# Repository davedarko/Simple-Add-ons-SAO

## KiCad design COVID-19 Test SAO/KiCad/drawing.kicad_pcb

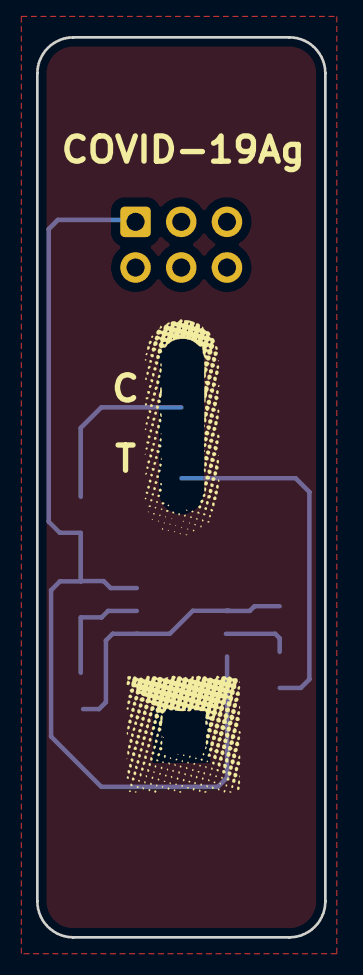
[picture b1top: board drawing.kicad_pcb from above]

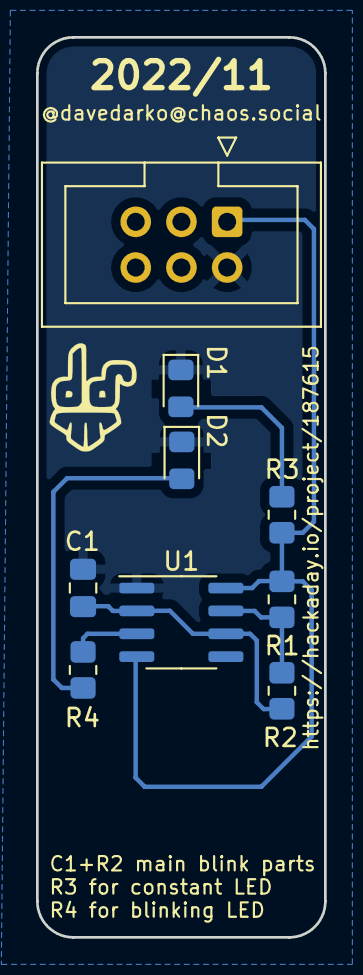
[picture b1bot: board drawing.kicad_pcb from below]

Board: 2 copper layers, 16.0 x 50.0 mm, 11 parts (10 on the bottom side), 7 nets.

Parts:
C1: 1uF; C_0805_2012Metric_Pad1.18x1.45mm_HandSolder
D1, D2: LED; LED_0805_2012Metric_Pad1.15x1.40mm_HandSolder
J1: Conn_02x03_Odd_Even; IDC-Header_2x03_P2.54mm_Vertical
R1, R3, R4: 1k; R_0805_2012Metric_Pad1.20x1.40mm_HandSolder
R2: 470k; R_0805_2012Metric_Pad1.20x1.40mm_HandSolder
Ref**: Val**; finalShadow
Ref**#2: Val**; davedarko_logo_silk_ext
U1: NE555D; SOIC-8_3.9x4.9mm_P1.27mm

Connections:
GND: C1.2, D1.1 (K), D2.1 (K), J1.2, U1.1 (GND)
unnamed: C1.1, R2.2, U1.2 (TR), U1.6 (THR)
unnamed: D1.2 (A), R3.2
unnamed: D2.2 (A), R4.2
unnamed: R1.2, R2.1, U1.7 (DIS)
unnamed: R4.1, U1.3 (Q)
VCC: J1.1, R1.1, R3.1, U1.4 (R), U1.8 (VCC)

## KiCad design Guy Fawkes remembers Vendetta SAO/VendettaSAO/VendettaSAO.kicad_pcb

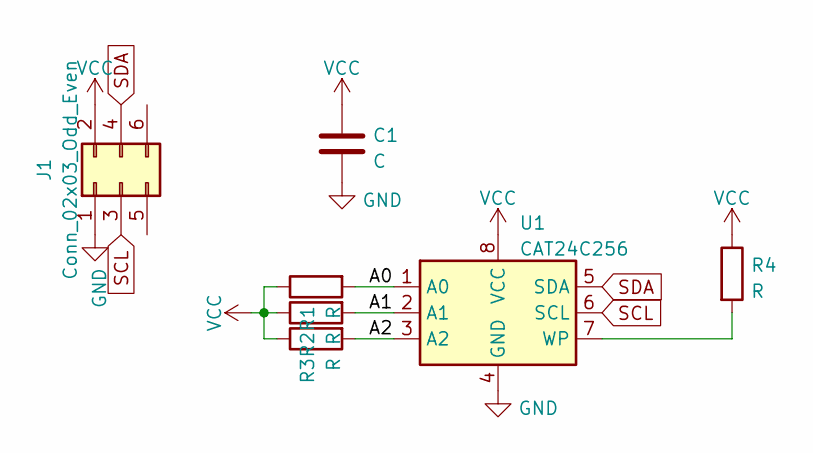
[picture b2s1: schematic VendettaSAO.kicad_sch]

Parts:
C1: C; C_0805_2012Metric_Pad1.18x1.45mm_HandSolder
J1: Conn_02x03_Odd_Even; PinSocket_2x03_P2.54mm_Vertical_SMD
R1, R2, R3, R4: R; R_0805_2012Metric_Pad1.20x1.40mm_HandSolder
U1: CAT24C256; SOIC-8_5.23x5.23mm_P1.27mm

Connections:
/A0: R1.2, U1.1 (A0)
/A1: R2.2, U1.2 (A1)
/A2: R3.2, U1.3 (A2)
GND: C1.2, J1.1, U1.4 (GND)
unnamed: R4.2, U1.7 (WP)
SCL: J1.3, U1.6 (SCL)
SDA: J1.4, U1.5 (SDA)
VCC: C1.1, J1.2, R1.1, R2.1, R3.1, R4.1, U1.8 (VCC)

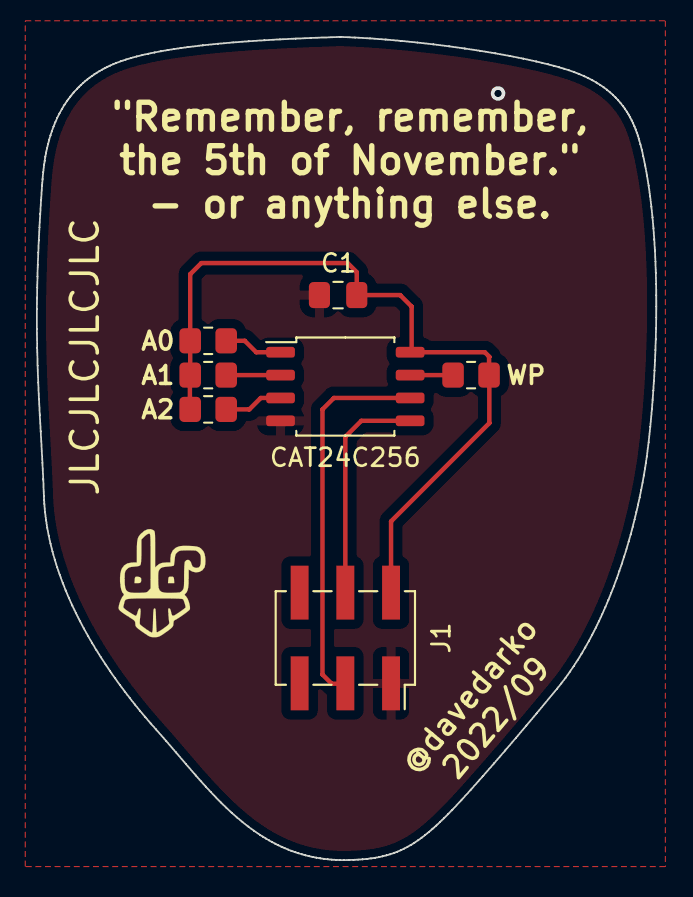
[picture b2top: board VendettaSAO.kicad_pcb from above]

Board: 2 copper layers, 34.4 x 45.7 mm, 10 parts (2 on the bottom side), 8 nets.

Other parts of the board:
Ref**: Val**; davedarko_logo_silk_outline
Ref**#2: Val**; vendettaSAO
Ref**#3: Val**; vendettaSAO_outline

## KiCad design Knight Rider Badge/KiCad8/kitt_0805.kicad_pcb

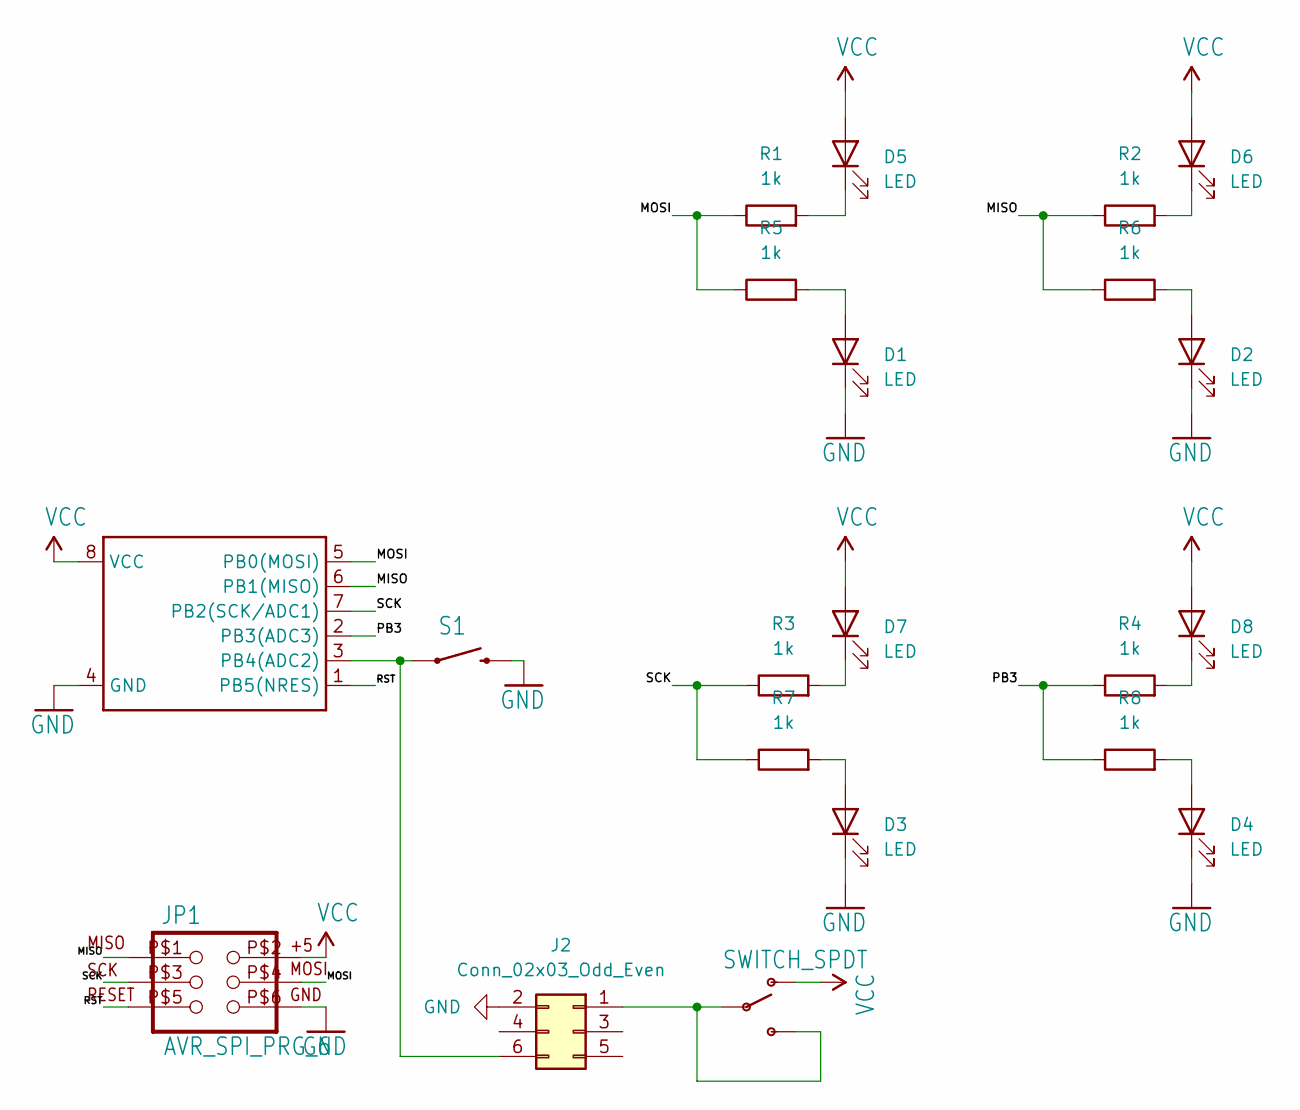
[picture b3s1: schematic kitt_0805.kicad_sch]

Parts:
D1, D2, D3, D4, D5, D6, D7, D8: LED; LED_0603_1608Metric_Pad1.05x0.95mm_HandSolder
J2: Conn_02x03_Odd_Even; IDC-Header_2x03_P2.54mm_Vertical_SMD
JP1: AVR_SPI_PRG_6; 2X3_SMD_PAD
R1, R2, R3, R4, R5, R6, R7, R8: 1k; R_0603_1608Metric_Pad0.98x0.95mm_HandSolder
S1: SWITCH-MOMENTARY-2-SMD-1101NE; TACTILE-SWITCH-1101NE
U1: Tiny85-20-SMT; SO08-EIAJ
U$1: SWITCH_SPDT; KPS-1290

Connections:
/MISO: JP1.P$1 (1), R2.1, R6.1, U1.6 (PB1(MISO))
/MOSI: JP1.P$4 (4), R1.1, R5.1, U1.5 (PB0(MOSI))
/PB3: R4.1, R8.1, U1.2 (PB3(ADC3))
/RST: JP1.P$5 (5), U1.1 (PB5(NRES))
/SCK: JP1.P$3 (3), R3.1, R7.1, U1.7 (PB2(SCK/ADC1))
GND: D1.1 (K), D2.1 (K), D3.1 (K), D4.1 (K), J2.2, JP1.P$6 (6), S1.P$2 (2), U1.4 (GND)
unnamed: D1.2 (A), R5.2
unnamed: D2.2 (A), R6.2
unnamed: D3.2 (A), R7.2
unnamed: D4.2 (A), R8.2
unnamed: D5.1 (K), R1.2
unnamed: D6.1 (K), R2.2
unnamed: D7.1 (K), R3.2
unnamed: D8.1 (K), R4.2
unnamed: J2.1, U$1.P, U$1.S
unnamed: J2.6, S1.P$1 (1), U1.3 (PB4(ADC2))
VCC: D5.2 (A), D6.2 (A), D7.2 (A), D8.2 (A), JP1.P$2 (2), U1.8 (VCC), U$1.O

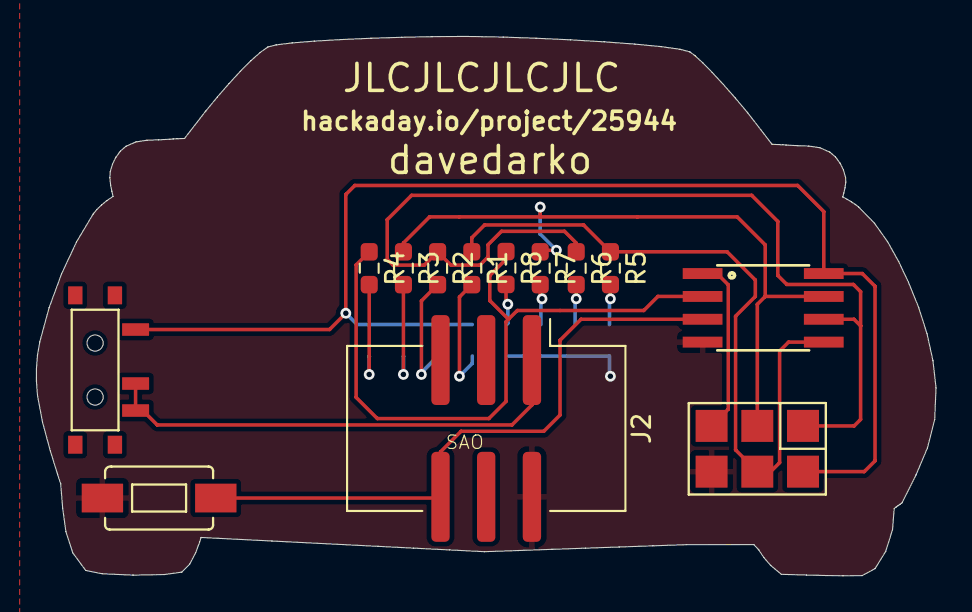
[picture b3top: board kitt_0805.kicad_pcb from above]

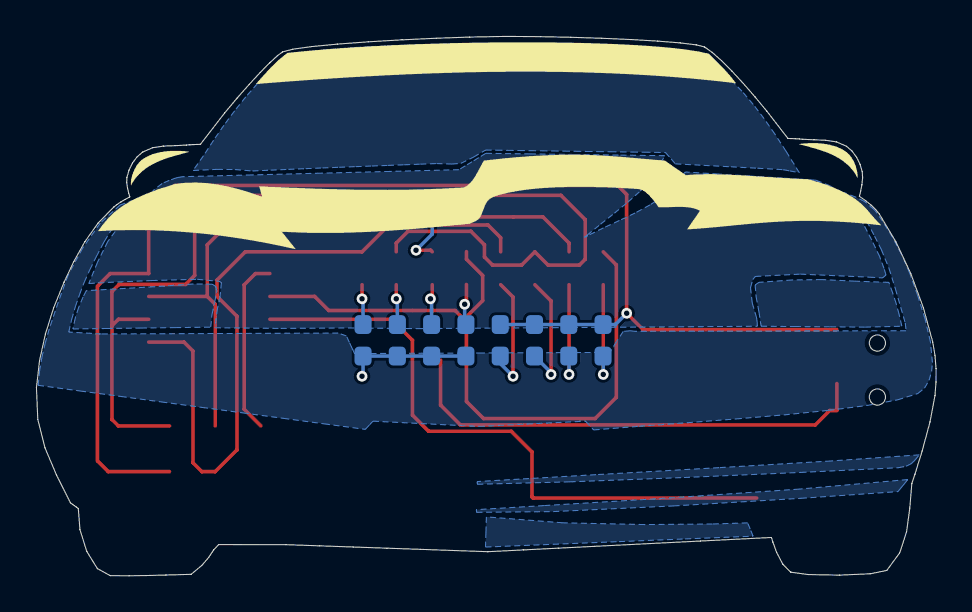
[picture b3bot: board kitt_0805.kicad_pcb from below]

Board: 2 copper layers, 50.0 x 30.0 mm, 21 parts (8 on the bottom side), 17 nets.

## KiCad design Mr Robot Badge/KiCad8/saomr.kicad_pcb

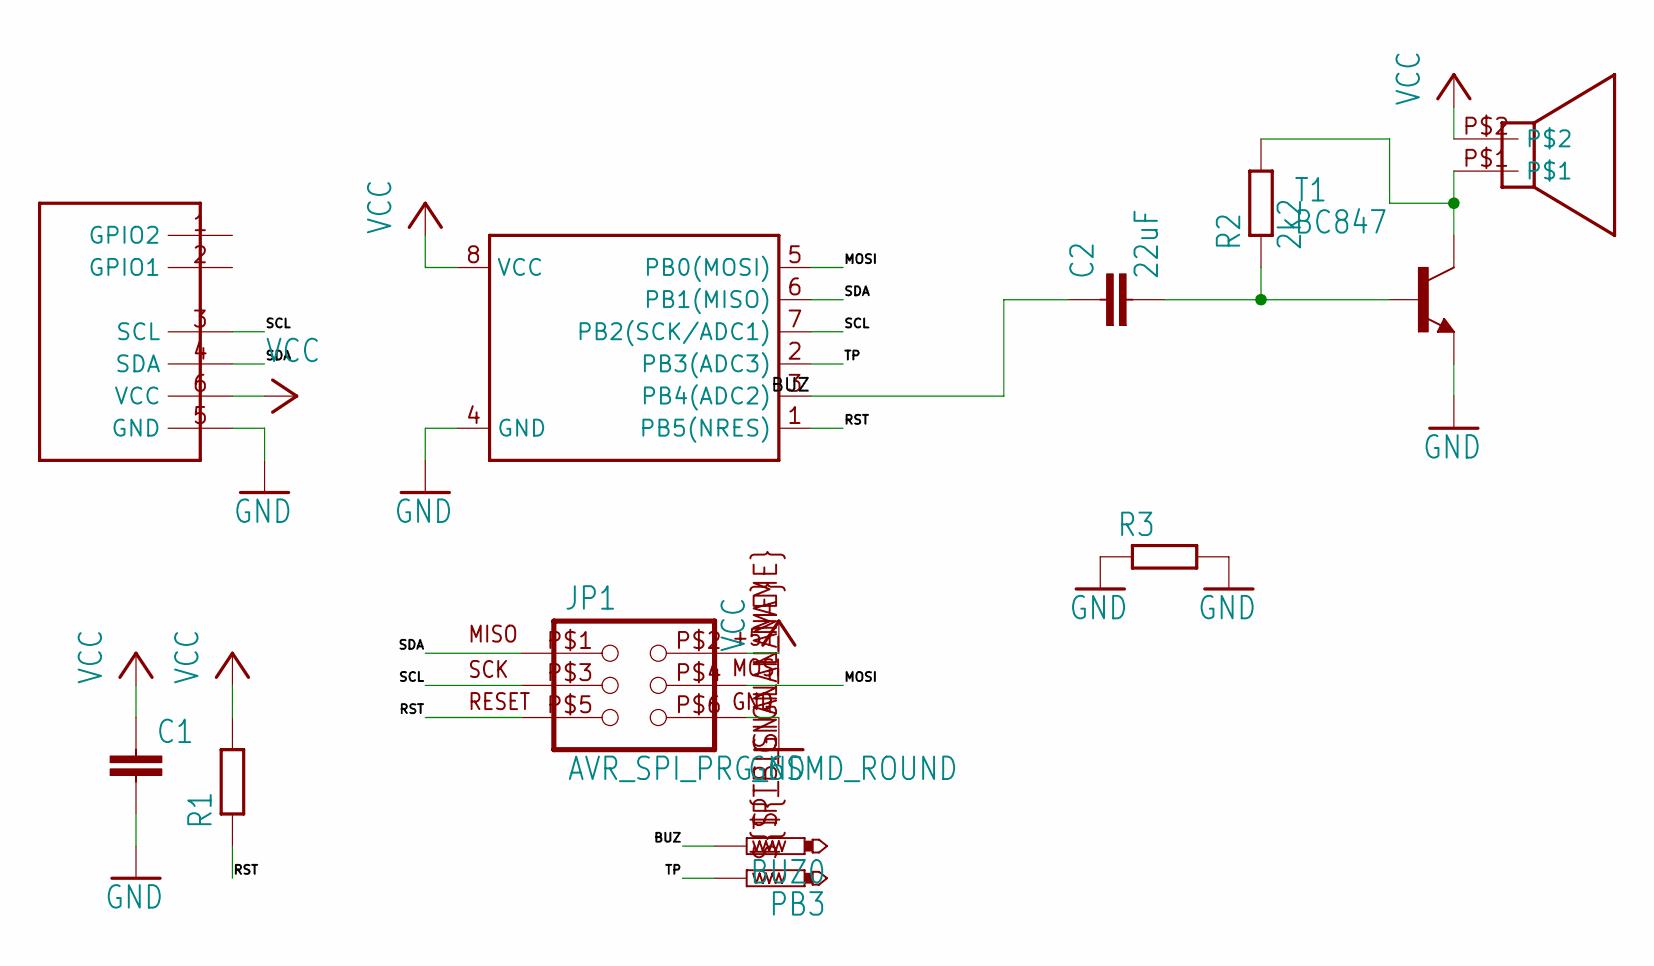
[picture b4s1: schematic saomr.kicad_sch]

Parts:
BUZ0: PTR1B2,54; B2,54
C1: C-EUC1206; C1206
C2: 22uF; C1206
JP1: AVR_SPI_PRG_6SMD_ROUND; 2X3_SMD_PAD_ROUND
PB3: PTR1B2,54; B2,54
R1: R-EU_R1206; R1206
R2: 2k2; R1206
R3: R-EU_M1206; M1206
T1: BC847; SOT23
U1: Tiny85-20-SMT; SO08-EIAJ
U$1: SPEAKERKMTG-1102; KMTG-1102
U$2: SAO-SHITTY-ADDON; 2X3_SMD

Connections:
unnamed: JP1.P$3 (3), U1.7 (PB2(SCK/ADC1)), U$2.3 (SCL)
unnamed: JP1.P$1 (1), U1.6 (PB1(MISO)), U$2.4 (SDA)
unnamed: C1.1, JP1.P$2 (2), R1.2, U1.8 (VCC), U$1.P$2, U$2.6 (VCC)
unnamed: C1.2, JP1.P$6 (6), R3.1, R3.2, T1.2 (E), U1.4 (GND), U$2.5 (GND)
unnamed: BUZ0.TP, C2.1, U1.3 (PB4(ADC2))
unnamed: JP1.P$5 (5), R1.1, U1.1 (PB5(NRES))
unnamed: JP1.P$4 (4), U1.5 (PB0(MOSI))
SCL: PB3.TP, U1.2 (PB3(ADC3))
SDA: C2.2, R2.1, T1.1 (B)
VCC: R2.2, T1.3 (C), U$1.P$1

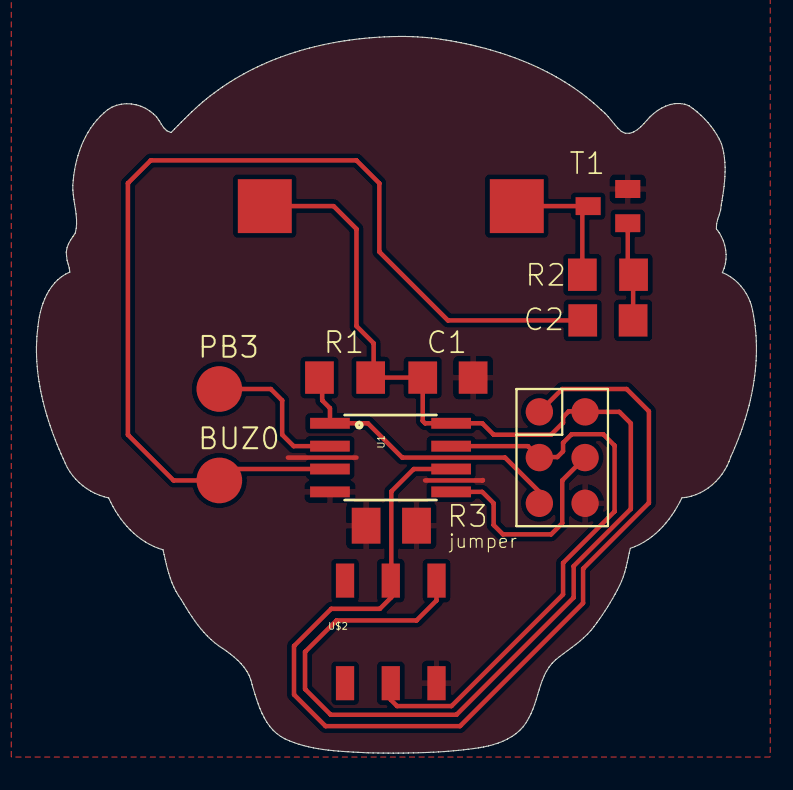
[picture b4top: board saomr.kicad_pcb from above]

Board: 2 copper layers, 40.0 x 39.8 mm, 13 parts (0 on the bottom side), 10 nets.

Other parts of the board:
U$3: DAVEDARKO_GOLD

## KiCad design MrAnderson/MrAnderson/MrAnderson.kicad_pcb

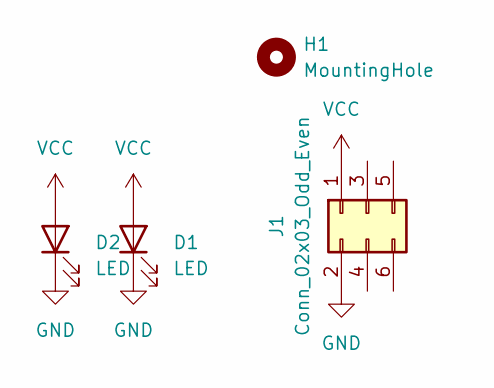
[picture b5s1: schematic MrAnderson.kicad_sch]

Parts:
D1, D2: LED; LED_1206_3216Metric_Pad1.42x1.75mm_HandSolder
H1: MountingHole; fingerboard_trucks
J1: Conn_02x03_Odd_Even; IDC-Header_2x03_P2.54mm_Vertical

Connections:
GND: D1.1 (K), D2.1 (K), J1.2
VCC: D1.2 (A), D2.2 (A), J1.1

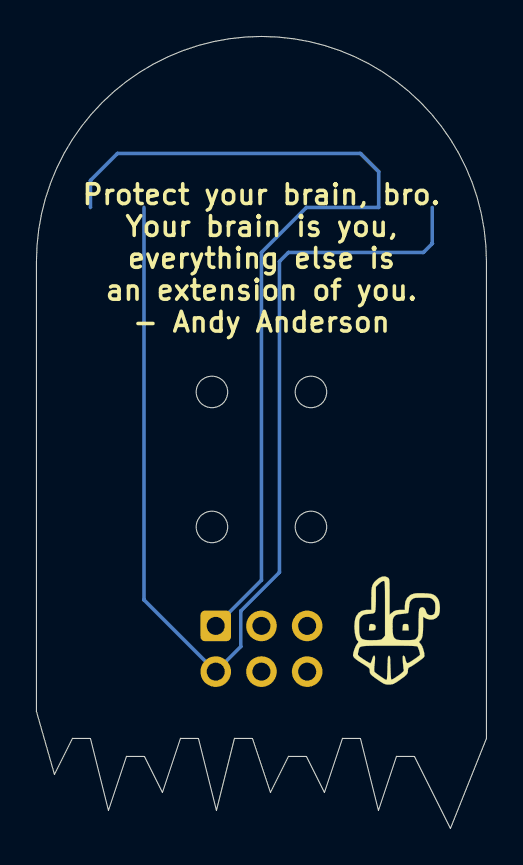
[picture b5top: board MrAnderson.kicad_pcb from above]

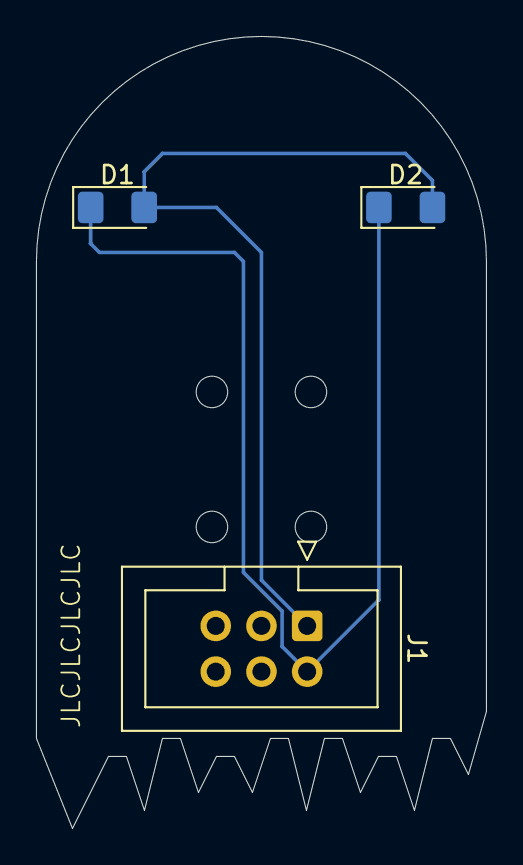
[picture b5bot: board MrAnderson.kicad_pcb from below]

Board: 2 copper layers, 25.0 x 44.0 mm, 5 parts (3 on the bottom side), 2 nets.

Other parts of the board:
Ref**: Val**; davedarko_logo_silk_outline
